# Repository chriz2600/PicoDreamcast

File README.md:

# PicoDreamcast

Small adapter board to easily hook up a PicoPSU to the Dreamcast

## Update

There was an issue, that the PicoPSU was not turning completely off, when PS_ON# was released, when no load is present on the 12V rail. The fix is to add a resistor (>10k) between 12V and GND.

The updated PCB includes this resistor.

## 

- **BOM**

    - **U1**: [Dreamcast power connector](https://www.digikey.com/product-detail/en/molex-connector-corporation/09-48-3064/WM13523-ND/863357)

    - **U2**: [ATX connector](https://www.aliexpress.com/item/5pcs-Motherboard-ATX-4-2-mm-24-pin-Male-Header-Pins-24-P-Mainboard-CPU-Power/32854035770.html)

    - **J1**: [Dreamcast power switch connector](https://www.digikey.com/product-detail/en/te-connectivity-amp-connectors/1-1123724-2/A106608-ND/686935)

    - [**PicoPSU**](http://www.mini-box.com/picoPSU-90)

    - [**Power supply**](https://www.amazon.de/gp/product/B00NWH1FTS/)

        *Any 12V 60+W power supply will do the job*

- **Gerber files**

    [`gerber.zip`](https://github.com/chriz2600/PicoDreamcast/blob/master/gerber.zip)

- **Power connector replacement**

    [SketchUp files](https://github.com/chriz2600/PicoDreamcast/tree/master/3dprinted)

##### Reference: [ATX12V Power Supply Design Guide](http://www.ieca-inc.com/images/ATX12V_PSDG2.0_Ratified.pdf)

#### 3.3.2 PS_ON#

PS_ON# is an active-low, TTL-compatible signal that allows a motherboard to remotely
control the power supply in conjunction with features such as soft on/off, Wake on LAN*,
or wake-on-modem. When PS_ON# is pulled to TTL low, the power supply should turn on
the five main DC output rails: +12VDC, +5VDC, +3.3VDC, -5VDC, and -12VDC. When
PS_ON# is pulled to TTL high or open-circuited, the DC output rails should not deliver
current and should be held at zero potential with respect to ground. PS_ON# has no effect
on the +5VSB output, which is always enabled whenever the AC power is present. Table
14 lists PS_ON# signal characteristics.

The power supply shall provide an internal pull-up to TTL high. The power supply shall
also provide de-bounce circuitry on PS_ON# to prevent it from oscillating on/off at startup
when activated by a mechanical switch. The DC output enable circuitry must be SELVcompliant.

The power supply shall not latch into a shutdown state when PS_ON# is driven active by
pulses between 10ms to 100ms during the decay of the power rails. 

---

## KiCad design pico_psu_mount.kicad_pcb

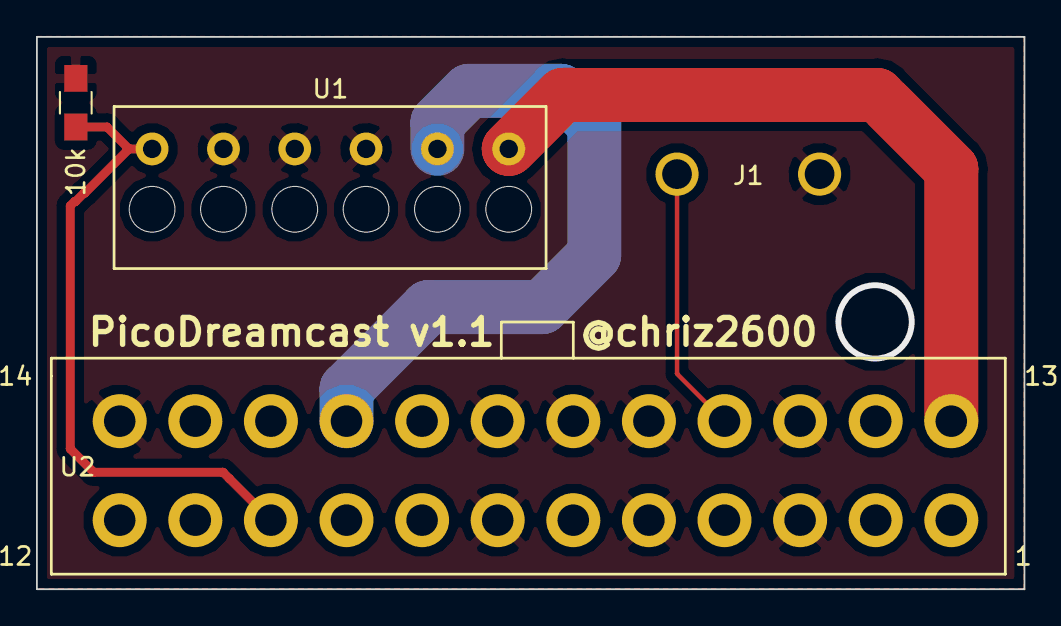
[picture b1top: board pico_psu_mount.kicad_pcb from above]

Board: 2 copper layers, 54.9 x 30.7 mm, 4 parts (0 on the bottom side), 5 nets.

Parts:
10k: R; R_0805_HandSoldering
J1: Conn_01x02; AMP-1-1123724-2
U1: DreamcastPower
U2: atx_24pin; ATX_24_pin

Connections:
/3.3V: U1.1, U2.13
/5V: U1.2, U2.21
/12V: 10k.1, U1.6, U2.10
/nPSon: J1.1, U2.16
GND: 10k.2, J1.2, U1.3, U1.4, U1.5, U2.3, U2.5, U2.7, U2.15, U2.17, U2.18, U2.19, U2.24

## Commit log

2018-11-29 added atx power supply reference on nPS_ON
2018-11-30 Create LICENSE
2018-12-11 fixed: PicoPSU does not turns off properly, when no load is present on the 12V rail
